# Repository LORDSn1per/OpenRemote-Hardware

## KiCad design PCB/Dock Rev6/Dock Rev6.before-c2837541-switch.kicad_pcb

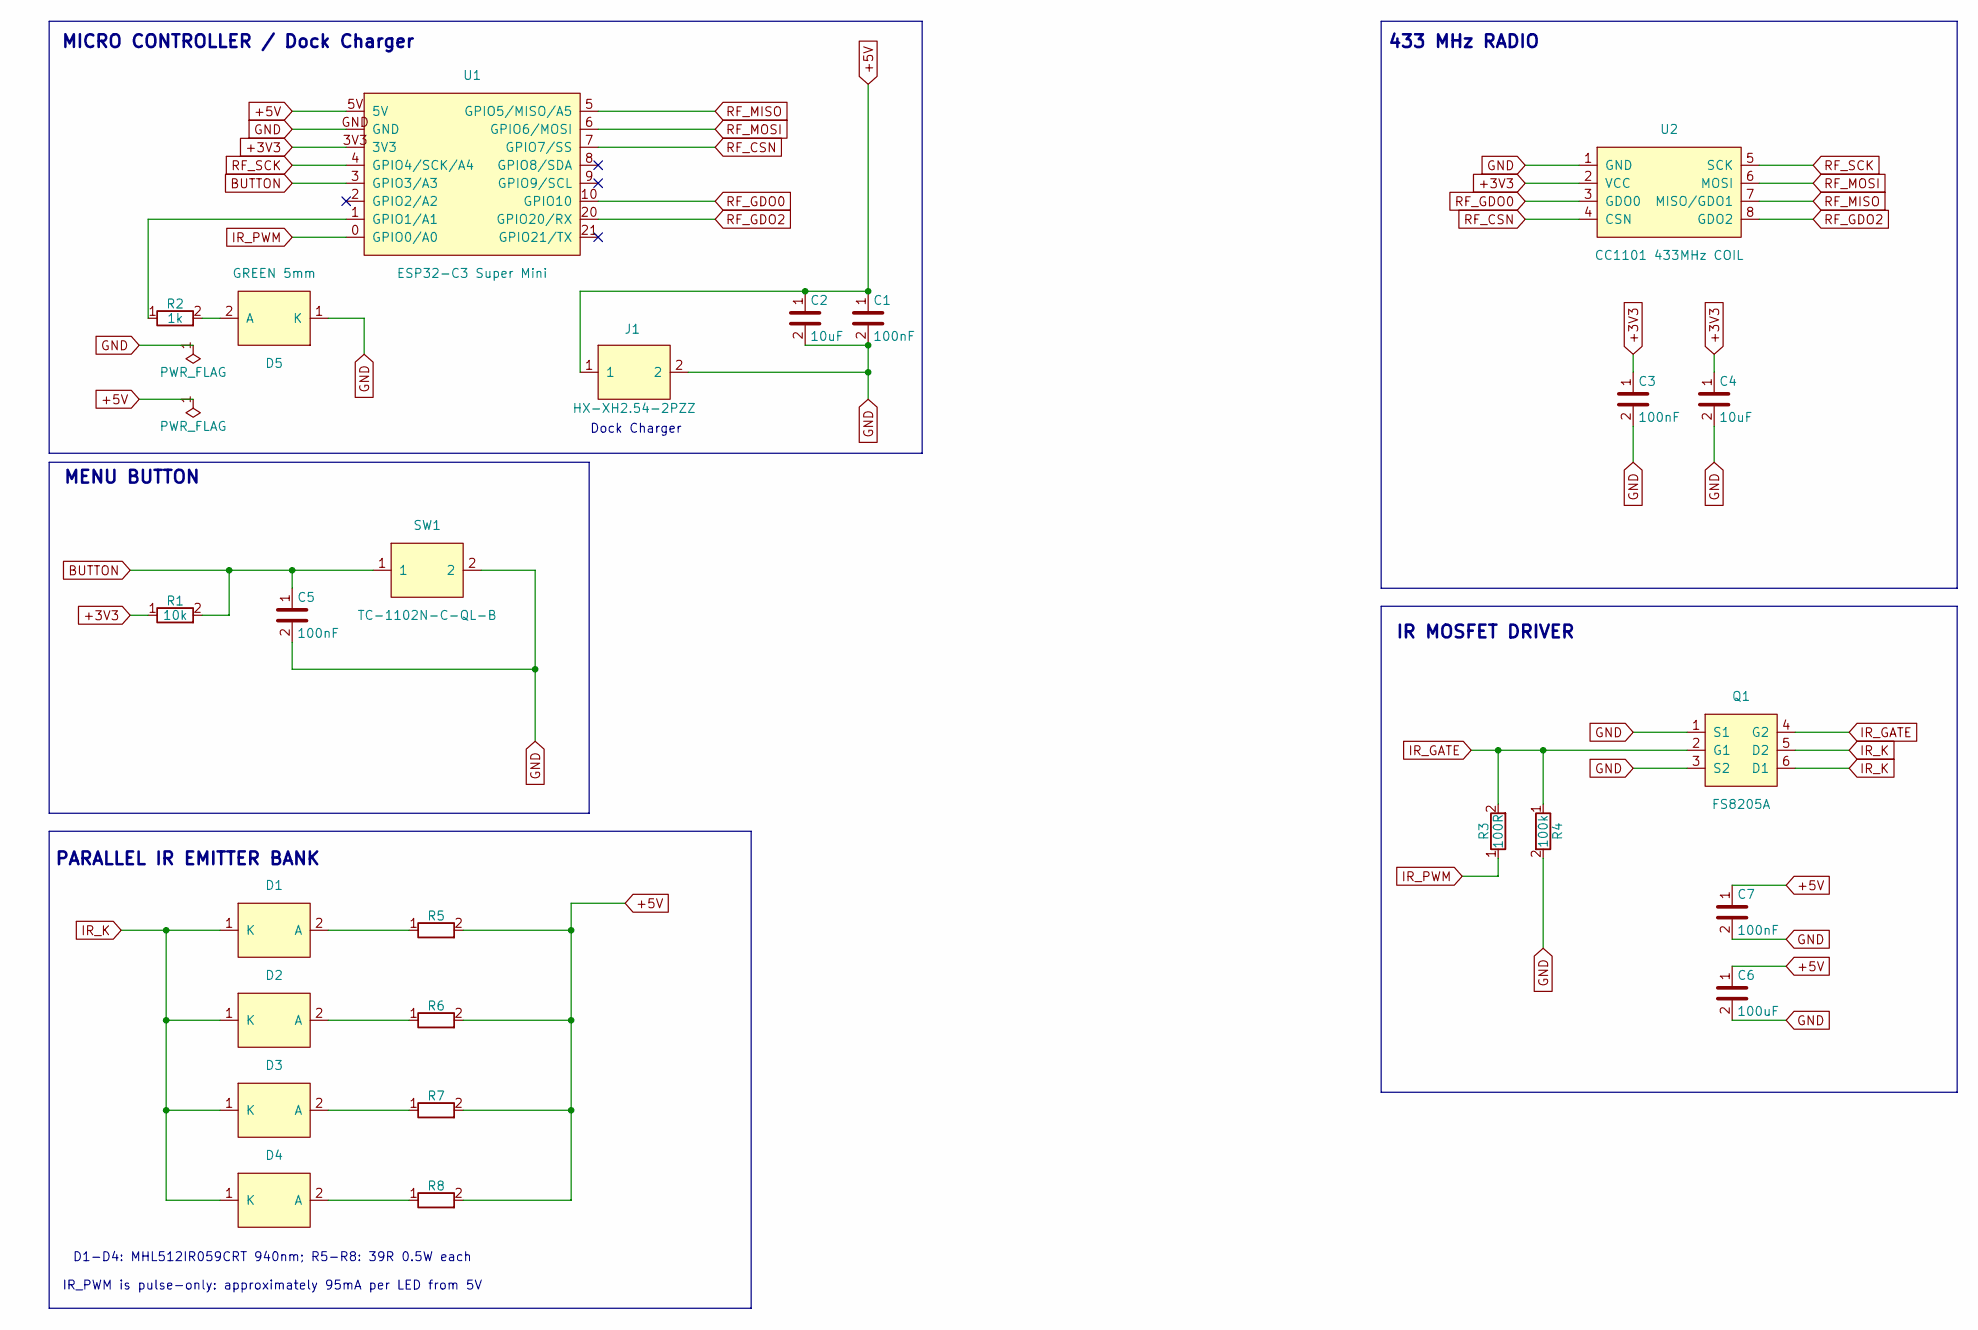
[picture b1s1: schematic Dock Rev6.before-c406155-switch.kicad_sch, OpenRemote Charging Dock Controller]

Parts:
C1, C3, C5, C7: 100nF; C_0603_1608Metric
C2, C4: 10uF; C_0805_2012Metric
C6: 100uF; CP_Radial_D5.0mm_P2.50mm
D1, D2, D3, D4: MHL512IR059CRT 940nm; LED_5mm_Side_Mount_C405273
D5: GREEN 5mm; LED_5mm_Green_THT
J1: HX-XH2.54-2PZZ; HX-XH2.54-2PZZ_C42391660
Q1: FS8205A; FS8205A_SOT-23-6
R1: 10k; R_0603_1608Metric
R2: 1k; R_0603_1608Metric
R3: 100R; R_0603_1608Metric
R4: 100k; R_0603_1608Metric
R5, R6, R7, R8: 39R 0.5W; R_Axial_DIN0411_L9.9mm_D3.6mm_P15.24mm_Horizontal
SW1: TC-1102N-C-QL-B; SW_TH_TC-1102N-C-QL-B_C406155
U1: ESP32-C3 Super Mini; ESP32-C3_SuperMini_Header_2x08_P2.54mm
U2: CC1101 433MHz COIL; CC1101_433MHz_Coil_Module_2x04_P2.54mm

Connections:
+3V3: C3.1, C4.1, R1.1, U1.3V3, U2.2 (VCC)
+5V: C1.1, C2.1, C6.1, C7.1, J1.1, R5.2, R6.2, R7.2, R8.2, U1.5V
BUTTON: C5.1, R1.2, SW1.1, U1.3 (GPIO3/A3)
GND: C1.2, C2.2, C3.2, C4.2, C5.2, C6.2, C7.2, D5.1 (K), J1.2, Q1.1 (S1), Q1.3 (S2), R4.2, SW1.2, U1.GND, U2.1 (GND)
IR_PWM: R3.1, U1.0 (GPIO0/A0)
unnamed: D1.2 (A), R5.1
unnamed: D2.2 (A), R6.1
unnamed: D3.2 (A), R7.1
unnamed: D4.2 (A), R8.1
unnamed: D5.2 (A), R2.2
unnamed: R2.1, U1.1 (GPIO1/A1)
RF_CSN: U1.7 (GPIO7/SS), U2.4 (CSN)
RF_GDO0: U1.10 (GPIO10), U2.3 (GDO0)
RF_GDO2: U1.20 (GPIO20/RX), U2.8 (GDO2)
RF_MISO: U1.5 (GPIO5/MISO/A5), U2.7 (MISO/GDO1)
RF_MOSI: U1.6 (GPIO6/MOSI), U2.6 (MOSI)
RF_SCK: U1.4 (GPIO4/SCK/A4), U2.5 (SCK)

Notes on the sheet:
PARALLEL IR EMITTER BANK
D1-D4: MHL512IR059CRT 940nm; R5-R8: 39R 0.5W each
IR MOSFET DRIVER
IR_PWM is pulse-only: approximately 95mA per LED from 5V
MENU BUTTON
433 MHz RADIO
Dock Charger
MICRO CONTROLLER / Dock Charger

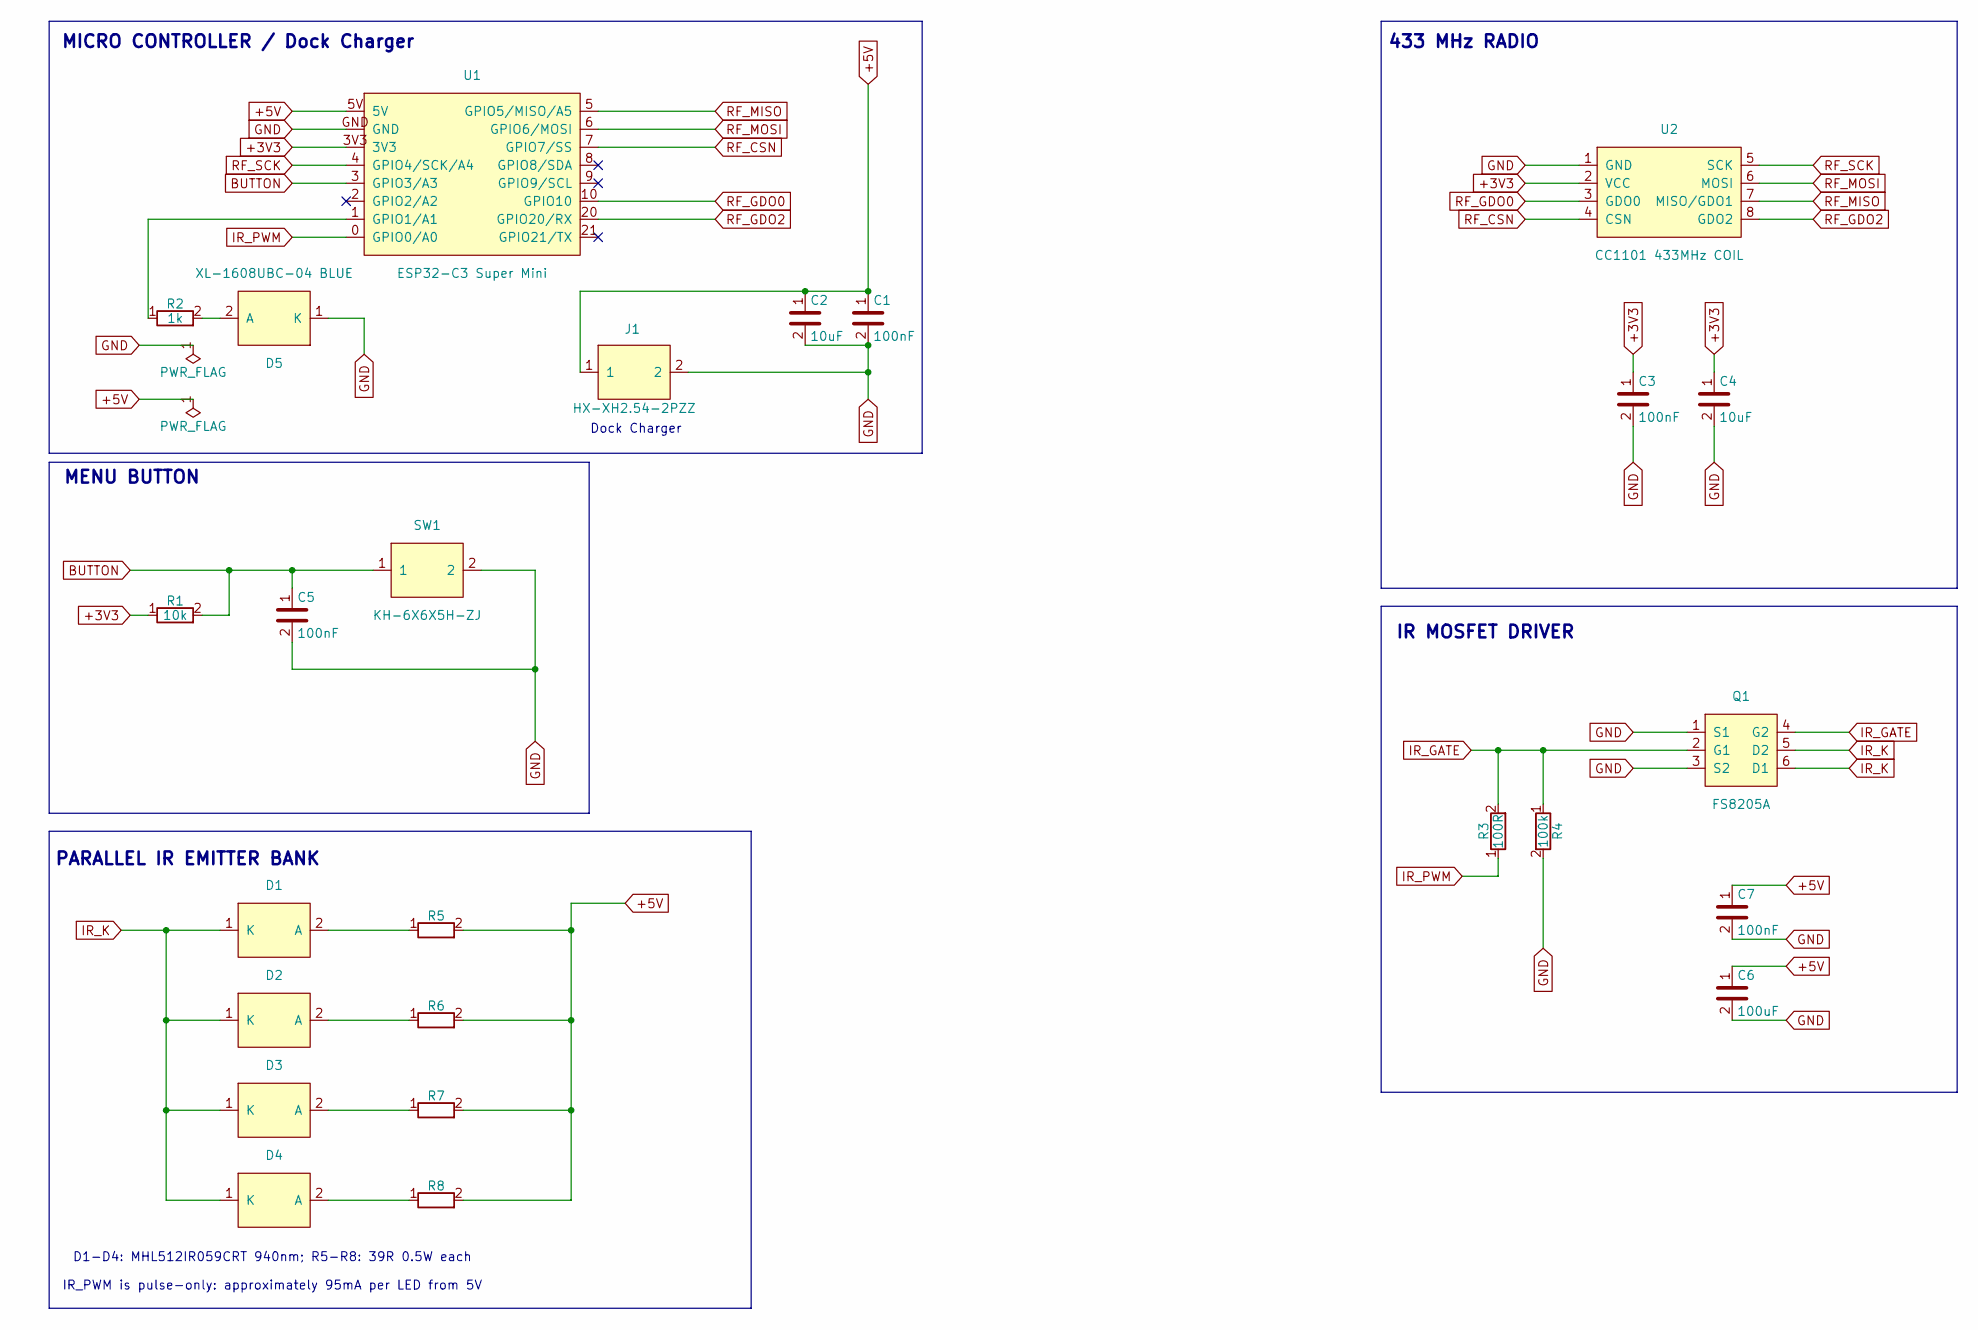
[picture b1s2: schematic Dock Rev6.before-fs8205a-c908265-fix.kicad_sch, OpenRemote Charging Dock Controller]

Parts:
C1, C3, C5, C7: 100nF; C_0603_1608Metric
C2, C4: 10uF; C_0805_2012Metric
C6: 100uF; CP_Radial_D5.0mm_P2.50mm
D1: MHL512IR059CRT 940nm; IR_LED_THT_D1_with_Assembly3D
D2, D3, D4: MHL512IR059CRT 940nm; LED_5mm_Green_THT
D5: XL-1608UBC-04 BLUE; LED_0603_1608Metric_NoSilk; LCSC C965807
J1: HX-XH2.54-2PZZ; HX-XH2.54-2PZZ_C42391660
Q1: FS8205A; FS8205A_SOT-23-6
R1: 10k; R_0603_1608Metric
R2: 1k; R_0603_1608Metric
R3: 100R; R_0603_1608Metric
R4: 100k; R_0603_1608Metric
R5, R6, R7, R8: 39R 0.5W; R_Axial_DIN0411_L9.9mm_D3.6mm_P15.24mm_Horizontal
SW1: KH-6X6X5H-ZJ; SW-TH_KH-6X6X5H-ZJ
U1: ESP32-C3 Super Mini; ESP32-C3_SuperMini_Header_2x08_P2.54mm
U2: CC1101 433MHz COIL; CC1101_433MHz_Coil_Module_2x04_P2.54mm

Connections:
+3V3: C3.1, C4.1, R1.1, U1.3V3, U2.2 (VCC)
+5V: C1.1, C2.1, C6.1, C7.1, J1.1, R5.2, R6.2, R7.2, R8.2, U1.5V
BUTTON: C5.1, R1.2, SW1.1, U1.3 (GPIO3/A3)
GND: C1.2, C2.2, C3.2, C4.2, C5.2, C6.2, C7.2, D5.1 (K), J1.2, Q1.1 (S1), Q1.3 (S2), R4.2, SW1.2, U1.GND, U2.1 (GND)
IR_PWM: R3.1, U1.0 (GPIO0/A0)
unnamed: D1.2 (A), R5.1
unnamed: D2.2 (A), R6.1
unnamed: D3.2 (A), R7.1
unnamed: D4.2 (A), R8.1
unnamed: D5.2 (A), R2.2
unnamed: R2.1, U1.1 (GPIO1/A1)
RF_CSN: U1.7 (GPIO7/SS), U2.4 (CSN)
RF_GDO0: U1.10 (GPIO10), U2.3 (GDO0)
RF_GDO2: U1.20 (GPIO20/RX), U2.8 (GDO2)
RF_MISO: U1.5 (GPIO5/MISO/A5), U2.7 (MISO/GDO1)
RF_MOSI: U1.6 (GPIO6/MOSI), U2.6 (MOSI)
RF_SCK: U1.4 (GPIO4/SCK/A4), U2.5 (SCK)

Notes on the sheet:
PARALLEL IR EMITTER BANK
D1-D4: MHL512IR059CRT 940nm; R5-R8: 39R 0.5W each
IR MOSFET DRIVER
IR_PWM is pulse-only: approximately 95mA per LED from 5V
MENU BUTTON
433 MHz RADIO
Dock Charger
MICRO CONTROLLER / Dock Charger

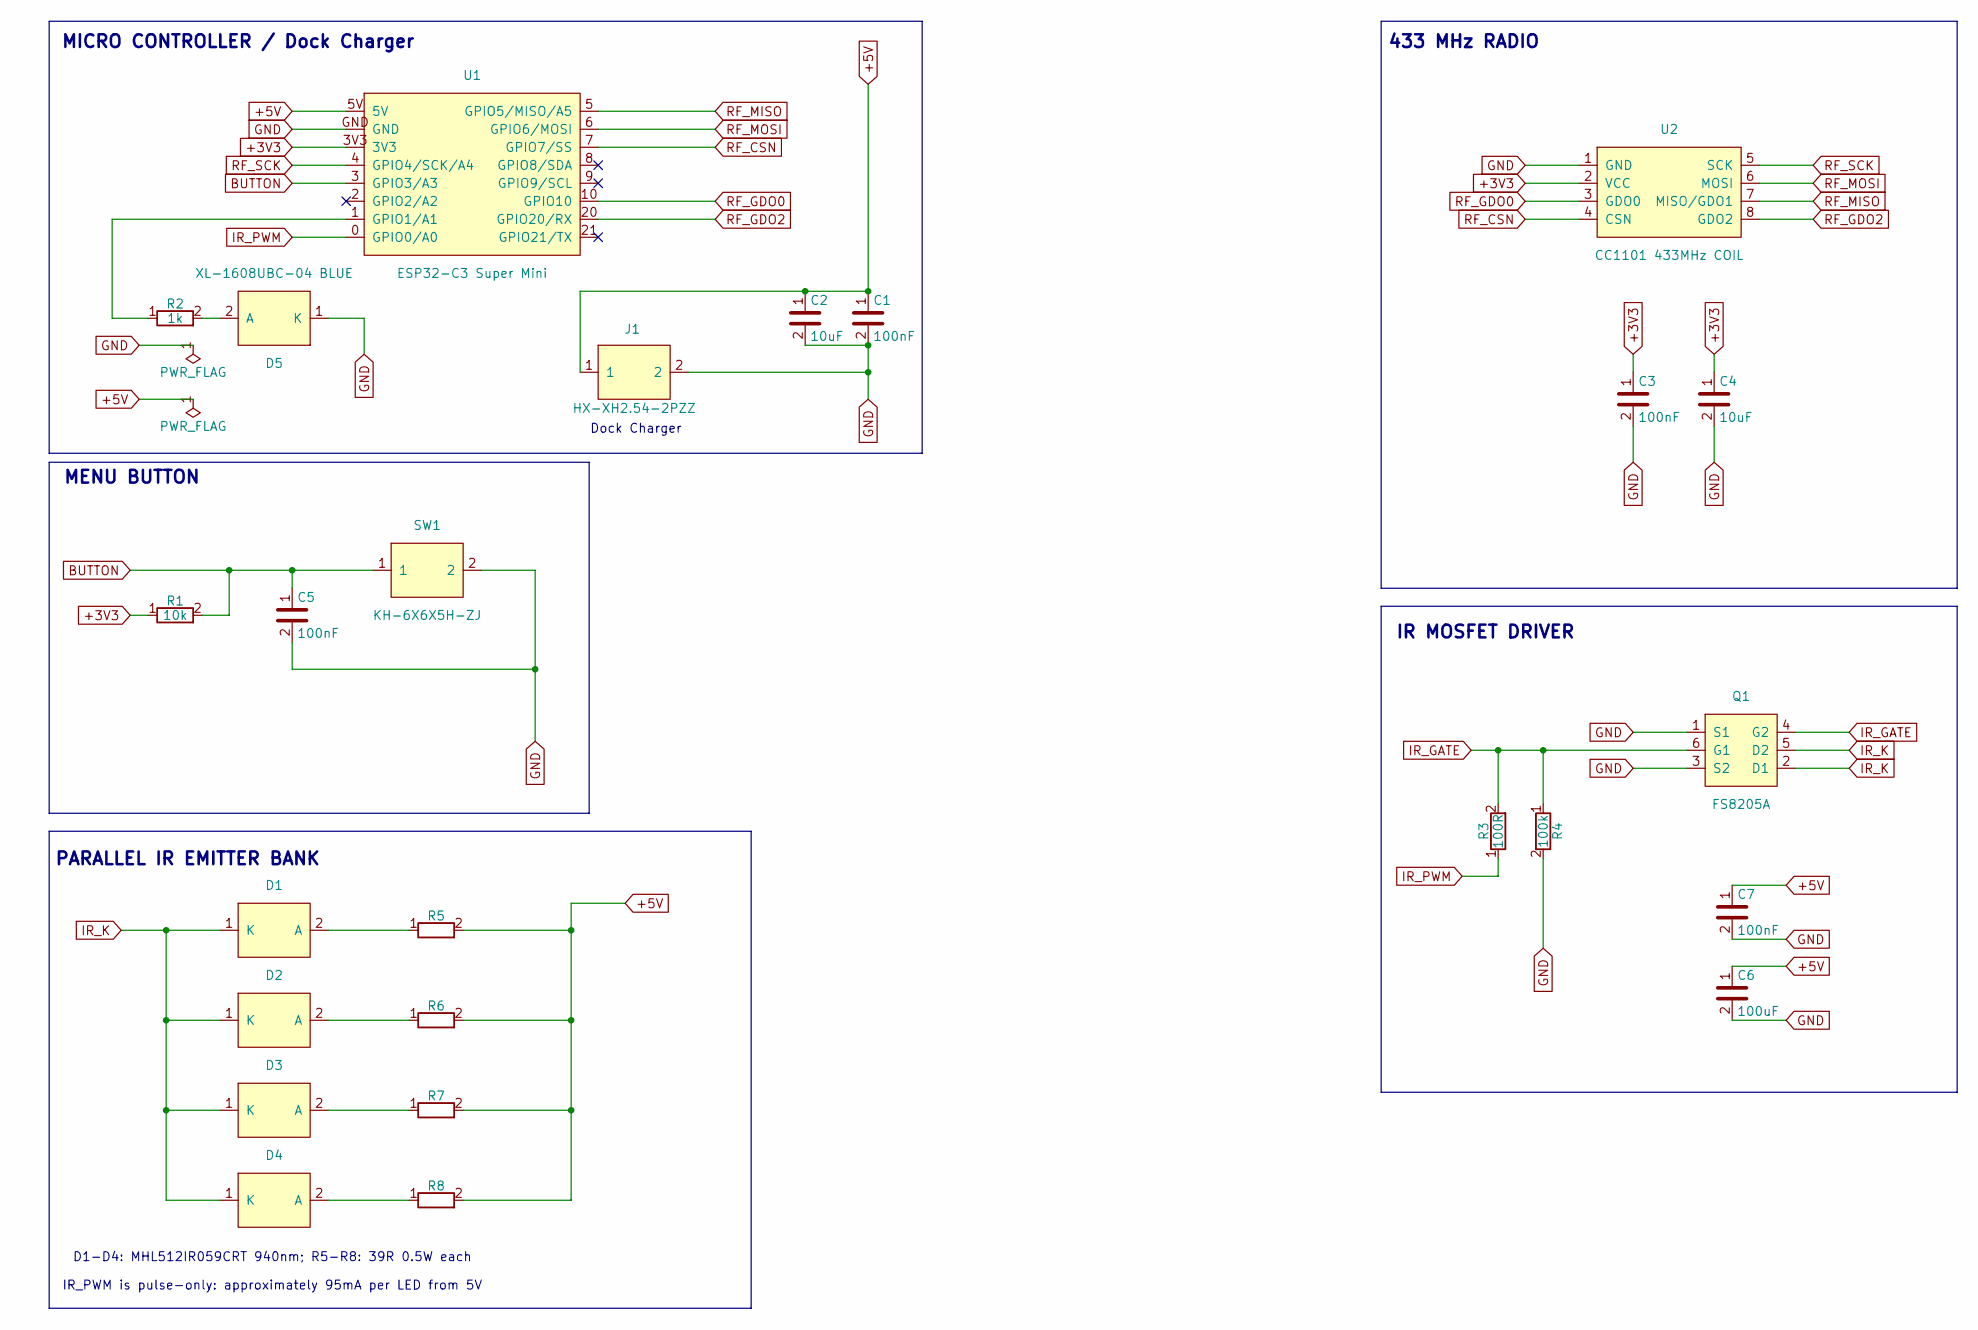
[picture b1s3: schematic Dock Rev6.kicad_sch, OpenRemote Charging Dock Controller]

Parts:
C1, C3, C5, C7: 100nF; C_0603_1608Metric
C2, C4: 10uF; C_0805_2012Metric
C6: 100uF; CP_Radial_D5.0mm_P2.50mm
D1: MHL512IR059CRT 940nm; IR_LED_THT_D1_with_Assembly3D
D2, D3, D4: MHL512IR059CRT 940nm; LED_5mm_Green_THT
D5: XL-1608UBC-04 BLUE; LED_0603_1608Metric_NoSilk; LCSC C965807
J1: HX-XH2.54-2PZZ; HX-XH2.54-2PZZ_C42391660
Q1: FS8205A; FS8205A_SOT-23-6
R1: 10k; R_0603_1608Metric
R2: 1k; R_0603_1608Metric
R3: 100R; R_0603_1608Metric
R4: 100k; R_0603_1608Metric
R5, R6, R7, R8: 39R 0.5W; R_Axial_DIN0411_L9.9mm_D3.6mm_P15.24mm_Horizontal
SW1: KH-6X6X5H-ZJ; SW-TH_KH-6X6X5H-ZJ
U1: ESP32-C3 Super Mini; ESP32-C3_SuperMini_Header_2x08_P2.54mm
U2: CC1101 433MHz COIL; CC1101_433MHz_Coil_Module_2x04_P2.54mm

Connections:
+3V3: C3.1, C4.1, R1.1, U1.3V3, U2.2 (VCC)
+5V: C1.1, C2.1, C6.1, C7.1, J1.1, R5.2, R6.2, R7.2, R8.2, U1.5V
BUTTON: C5.1, R1.2, SW1.1, U1.3 (GPIO3/A3)
GND: C1.2, C2.2, C3.2, C4.2, C5.2, C6.2, C7.2, D5.1 (K), J1.2, Q1.1 (S1), Q1.3 (S2), R4.2, SW1.2, U1.GND, U2.1 (GND)
IR_PWM: R3.1, U1.0 (GPIO0/A0)
unnamed: D1.2 (A), R5.1
unnamed: D2.2 (A), R6.1
unnamed: D3.2 (A), R7.1
unnamed: D4.2 (A), R8.1
unnamed: D5.2 (A), R2.2
unnamed: R2.1, U1.1 (GPIO1/A1)
RF_CSN: U1.7 (GPIO7/SS), U2.4 (CSN)
RF_GDO0: U1.10 (GPIO10), U2.3 (GDO0)
RF_GDO2: U1.20 (GPIO20/RX), U2.8 (GDO2)
RF_MISO: U1.5 (GPIO5/MISO/A5), U2.7 (MISO/GDO1)
RF_MOSI: U1.6 (GPIO6/MOSI), U2.6 (MOSI)
RF_SCK: U1.4 (GPIO4/SCK/A4), U2.5 (SCK)

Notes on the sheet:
PARALLEL IR EMITTER BANK
D1-D4: MHL512IR059CRT 940nm; R5-R8: 39R 0.5W each
IR MOSFET DRIVER
IR_PWM is pulse-only: approximately 95mA per LED from 5V
MENU BUTTON
433 MHz RADIO
Dock Charger
MICRO CONTROLLER / Dock Charger

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
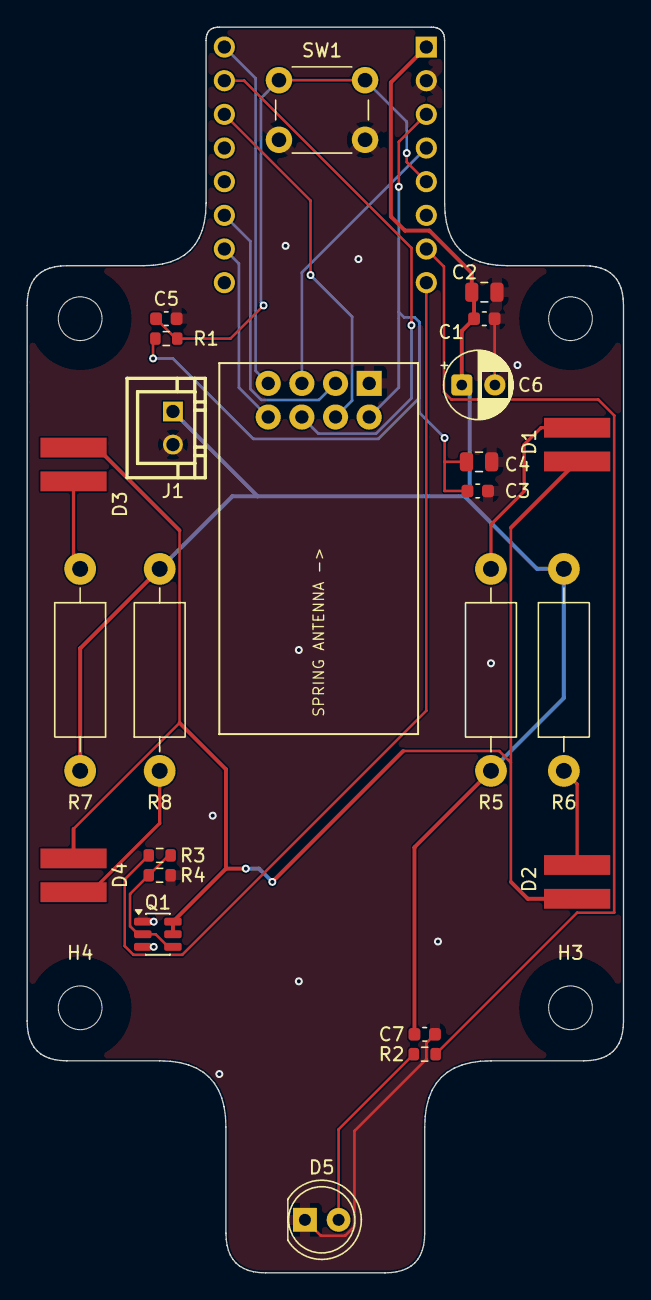
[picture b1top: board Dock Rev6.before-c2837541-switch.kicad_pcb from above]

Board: 2 copper layers, 45.0 x 94.0 mm, 29 parts (1 on the bottom side), 19 nets.

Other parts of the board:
H1, H2, H3, H4: M3x5 PCB SCREW / 3.3mm NPTH; MountingHole_3.2mm_M3

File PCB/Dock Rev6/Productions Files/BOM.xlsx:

﻿Designator | Value | Footprint | LCSC Part #
C1,C3,C5,C7 | 100nF | C_0603_1608Metric | C1591
C2,C4 | 10uF | C_0805_2012Metric | C15850
C6 | 100uF | CP_Radial_D5.0mm_P2.50mm
D1 | MHL512IR059CRT 940nm | IR_LED_THT_D1_with_Assembly3D | C405273
D2,D3,D4 | MHL512IR059CRT 940nm | LED_5mm_Green_THT | C405273
D5 | XL-1608UBC-04 BLUE | LED_0603_1608Metric_NoSilk | C965807
J1 | HX-XH2.54-2PZZ | HX-XH2.54-2PZZ_C42391660 | C42391660
Q1 | FS8205A | FS8205A_SOT-23-6 | C908265
R1 | 10k | R_0603_1608Metric | C98220
R2 | 1k | R_0603_1608Metric | C22548
R3 | 100R | R_0603_1608Metric
R4 | 100k | R_0603_1608Metric
R5,R6,R7,R8 | 39R 0.5W | R_Axial_DIN0411_L9.9mm_D3.6mm_P15.24mm_Horizontal
SW1 | KH-6X6X5H-ZJ | SW-TH_KH-6X6X5H-ZJ | C2837541
U1 | ESP32-C3 Super Mini | ESP32-C3_SuperMini_Header_2x08_P2.54mm
U2 | CC1101 433MHz COIL | CC1101_433MHz_Coil_Module_2x04_P2.54mm
